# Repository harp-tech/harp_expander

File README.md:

# Harp Input Expander
# Harp Output Expander

Harp board to expand the inputs and outputs of the current harp ecosystem.

# Licensing

The code, designs, documentation, and photos available in this repository is free: you can redistribute it and/or modify it under the terms of the used license.
Each subdirectory will contain a license or, possibly, a set of licenses if it involves both hardware and software. Check files named LICENSE.

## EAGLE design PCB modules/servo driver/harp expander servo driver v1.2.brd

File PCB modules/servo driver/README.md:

# Harp Expander Servo Driver

## Licensing

The designs, documentation, and photos available in this repository are free: you can redistribute it and/or modify it under the terms of the used license.
Check file named LICENSE.

Copyright Filipe Carvalho 2020-2021

<br />This work is licensed under a <a rel="license" href="http://creativecommons.org/licenses/by-nc-sa/3.0/igo/">Creative Commons Attribution-NonCommercial-ShareAlike 3.0 IGO License</a>.

If your are interested in obtaining a license to sell this device, please contact filipe@open-ephys.org

[1]: https://docs.google.com/spreadsheets/d/1aobmmEzBDethzIlrm1eg0eYkBqlyX3s9WbA9KgRwVQI/edit?usp=sharing

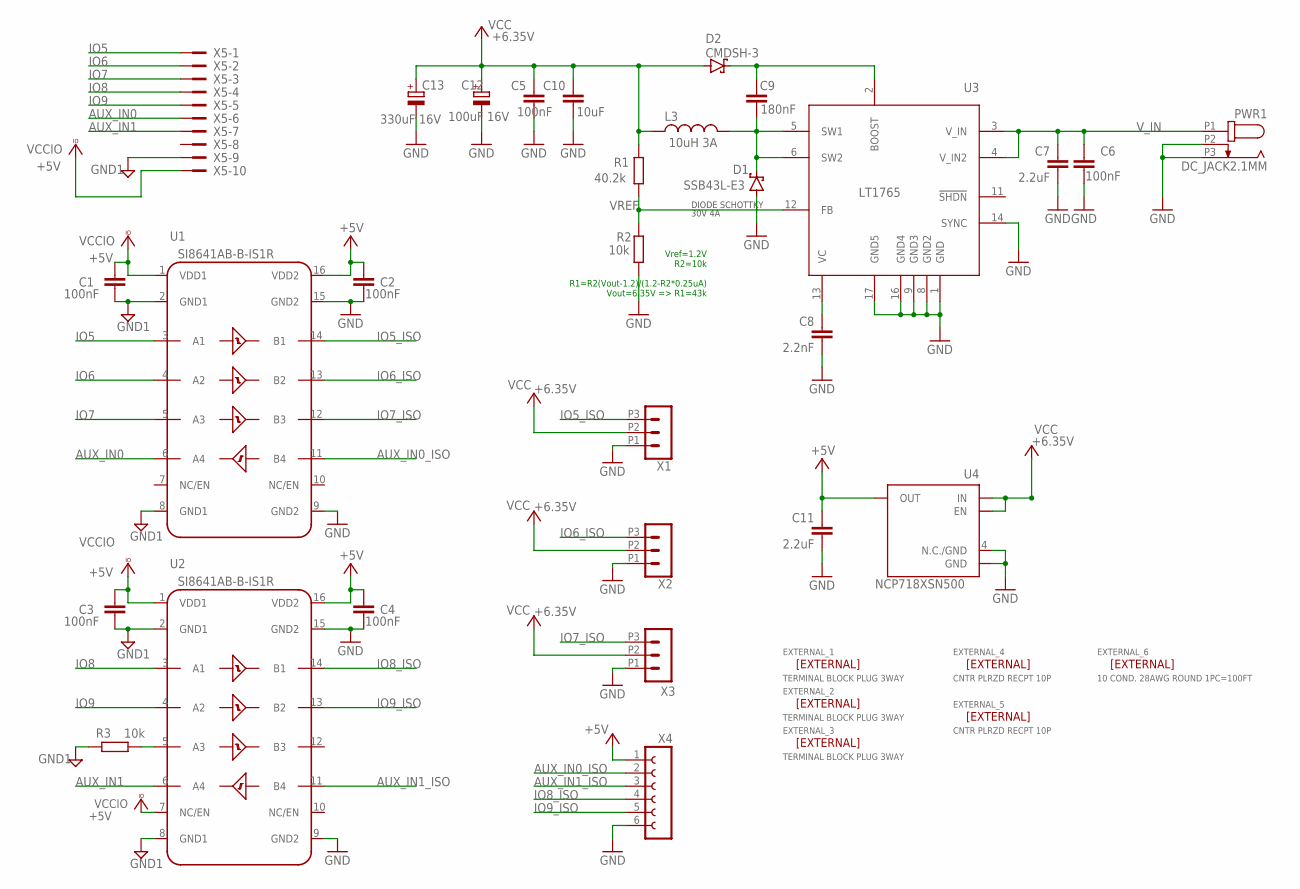
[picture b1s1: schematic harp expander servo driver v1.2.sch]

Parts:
C1, C2, C3, C4, C5, C6: 100nF; C0402; MPN CGA2B3X7R1H104K050BB; DIGIKEY_PN 445-6899-2-ND
C7, C11: 2.2uF; C0603; MPN GRM188R61E225MA12D; DIGIKEY_PN 490-12738-1-ND
C8: 2.2nF; C0402; MPN CL05B222JB5NNNC; DIGIKEY_PN 1276-1532-6-ND
C9: 180nF; C0603; MPN GCG188R91H184KA01D; DIGIKEY_PN 490-GCG188R91H184KA01DCT-ND
C10: 10uF; C0603; MPN EMK107BBJ106MA-T; DIGIKEY_PN 587-3238-1-ND
C12: 100uF 16V; CT7343; MPN T491D107K016AT7280; DIGIKEY_PN 399-18066-1-ND
C13: 330uF 16V; E3,5-8; MPN MCMR16V337M8X7; FARNELL_PN 1870957
D1: SSB43L-E3; SMB; MPN SSB43L-E3/52T; DIGIKEY_PN SSB43L-E3/52TGICT-ND
D2: CMDSH-3; SOD323-R; MPN CMDSH-3; DIGIKEY_PN 1514-CMDSH-3TRPBFREECT-ND
EXTERNAL_1, EXTERNAL_2, EXTERNAL_3: TERMINAL BLOCK PLUG 3WAY; -; MPN 691361100003; DIGIKEY_PN 732-2752-ND
EXTERNAL_4, EXTERNAL_5: CNTR PLRZD RECPT 10P; -; MPN 1658621-1; DIGIKEY_PN AKC10H-ND
EXTERNAL_6: 10 COND. 28AWG ROUND 1PC=100FT; -; MPN 3365/10 100; DIGIKEY_PN 3M157849-100-ND
L3: 10uH 3A; L_IHLP_PADS; MOUSER_PN 70-IHLP2525CZER100M0; DIGIKEY_PN 541-1013-2-ND
PWR1: DC_JACK2.1MM; DC_POWER_INPUT_2.1MM; MPN 163-179PH-EX; DIGIKEY_PN 163-179PH-EX MOUSER
R1: 40.2k; R0402; MPN RC0402FR-0740K2L; DIGIKEY_PN 311-40.2KLRCT-ND
R2, R3: 10k; R0402; MPN CRCW040210K0FKEDC; DIGIKEY_PN 541-3959-1-ND
U1, U2: SI8641AB-B-IS1R; SO16W; MOUSER_PN 634-SI8641AB-B-IS1R; DIGIKEY_PN SI8641AB-B-IS-ND
U3: LT1765; TSSOP16; MPN LT1765EFE#TRPBF; DIGIKEY_PN LT1765EFE#TRPBFCT-ND
U4: NCP718XSN500; SOT23-5; MPN NCP718BSN500T1G; DIGIKEY_PN NCP718BSN500T1GOSCT-ND
X1, X2, X3: CON_3.5MM_1X3; MPN 691322110003; DIGIKEY_PN 732-2770-ND
X4: aux_header; FE06; MPN n.a.
X5: IDC 10WAY STRAIGHT; PAK100/2500-10; MPN SBH11-PBPC-D05-ST-BK; DIGIKEY_PN S9169-ND

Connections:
+5V: C2.1, C4.1, C11.1, U1.16 (VDD2), U2.16 (VDD2), U4.5 (OUT), X4.1
AUX_IN0: U1.6 (A4), X5.6
AUX_IN0_ISO: U1.11 (B4), X4.2
AUX_IN1: U2.6 (A4), X5.7
AUX_IN1_ISO: U2.11 (B4), X4.3
GND: C2.2, C4.2, C5.2, C6.2, C7.2, C8.2, C10.2, C11.2, C12.-, C13.-, D1.A, PWR1.P2 (2), PWR1.P3 (3), R2.1, U1.9 (GND2), U1.15 (GND2), U2.9 (GND2), U2.15 (GND2), U3.1 (GND), U3.8 (GND2), U3.9 (GND3), U3.14 (SYNC), U3.16 (GND4), U3.17 (GND5), U4.2 (GND), U4.4 (N.C./GND), X1.P1 (1), X2.P1 (1), X3.P1 (1), X4.6
GND1: C1.2, C3.2, R3.2, U1.2 (GND1), U1.8 (GND1), U2.2 (GND1), U2.8 (GND1), X5.9
IO5: U1.3 (A1), X5.1
IO5_ISO: U1.14 (B1), X1.P3 (3)
IO6: U1.4 (A2), X5.2
IO6_ISO: U1.13 (B2), X2.P3 (3)
IO7: U1.5 (A3), X5.3
IO7_ISO: U1.12 (B3), X3.P3 (3)
IO8: U2.3 (A1), X5.4
IO8_ISO: U2.14 (B1), X4.4
IO9: U2.4 (A2), X5.5
IO9_ISO: U2.13 (B2), X4.5
unnamed: R3.1, U2.5 (A3)
unnamed: C8.1, U3.13 (VC)
unnamed: C9.2, D1.C, L3.2, U3.5 (SW1), U3.6 (SW2)
unnamed: C9.1, D2.C, U3.2 (BOOST)
VCC: C5.1, C10.1, C12.+, C13.+, D2.A, L3.1, R1.2, U4.1 (IN), U4.3 (EN), X1.P2 (2), X2.P2 (2), X3.P2 (2)
VCCIO: C1.1, C3.1, U1.1 (VDD1), U2.1 (VDD1), U2.7 (NC/EN), X5.10
VREF: R1.1, R2.2, U3.12 (FB)
V_IN: C6.1, C7.1, PWR1.P1 (1), U3.3 (V_IN), U3.4 (V_IN2)

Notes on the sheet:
Vref=1.2V R2=10k R1=R2(Vout-1.2)/(1.2-R2*0.25uA) Vout=6.35V => R1=43k
DIODE SCHOTTKY 30V 4A

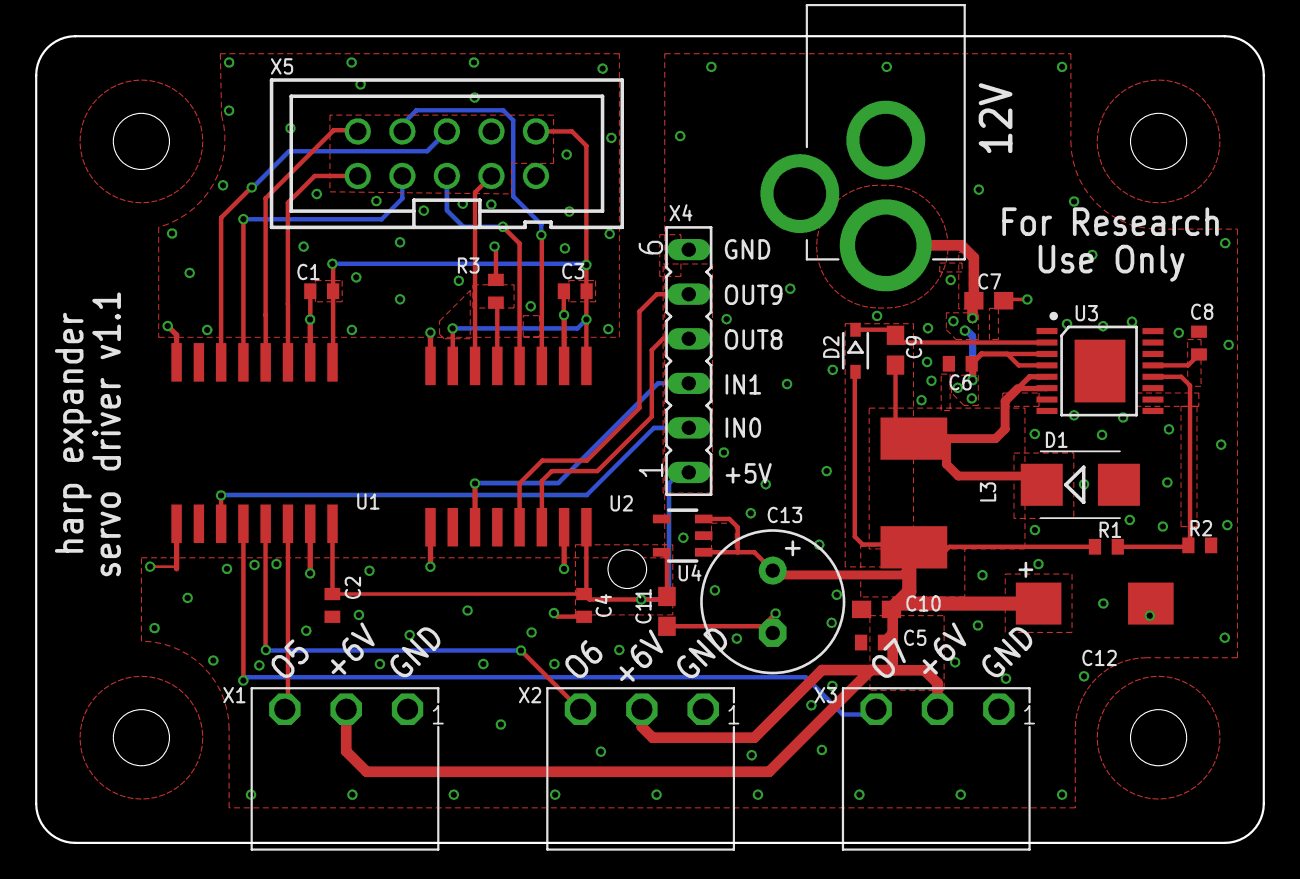
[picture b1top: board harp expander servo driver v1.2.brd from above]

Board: 2 copper layers, 70.0 x 46.0 mm, 35 parts (0 on the bottom side), 25 nets.

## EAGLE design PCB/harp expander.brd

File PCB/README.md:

# Harp Expander PCB

## Licensing

The designs, documentation, and photos available in this repository are free: you can redistribute it and/or modify it under the terms of the used license.
Check file named LICENSE.

Copyright Filipe Carvalho 2020-2021

<br />This work is licensed under a <a rel="license" href="http://creativecommons.org/licenses/by-nc-sa/3.0/igo/">Creative Commons Attribution-NonCommercial-ShareAlike 3.0 IGO License</a>.

If your are interested in obtaining a license to sell this device, please contact filipe@open-ephys.org

[1]: https://docs.google.com/spreadsheets/d/1aobmmEzBDethzIlrm1eg0eYkBqlyX3s9WbA9KgRwVQI/edit?usp=sharing

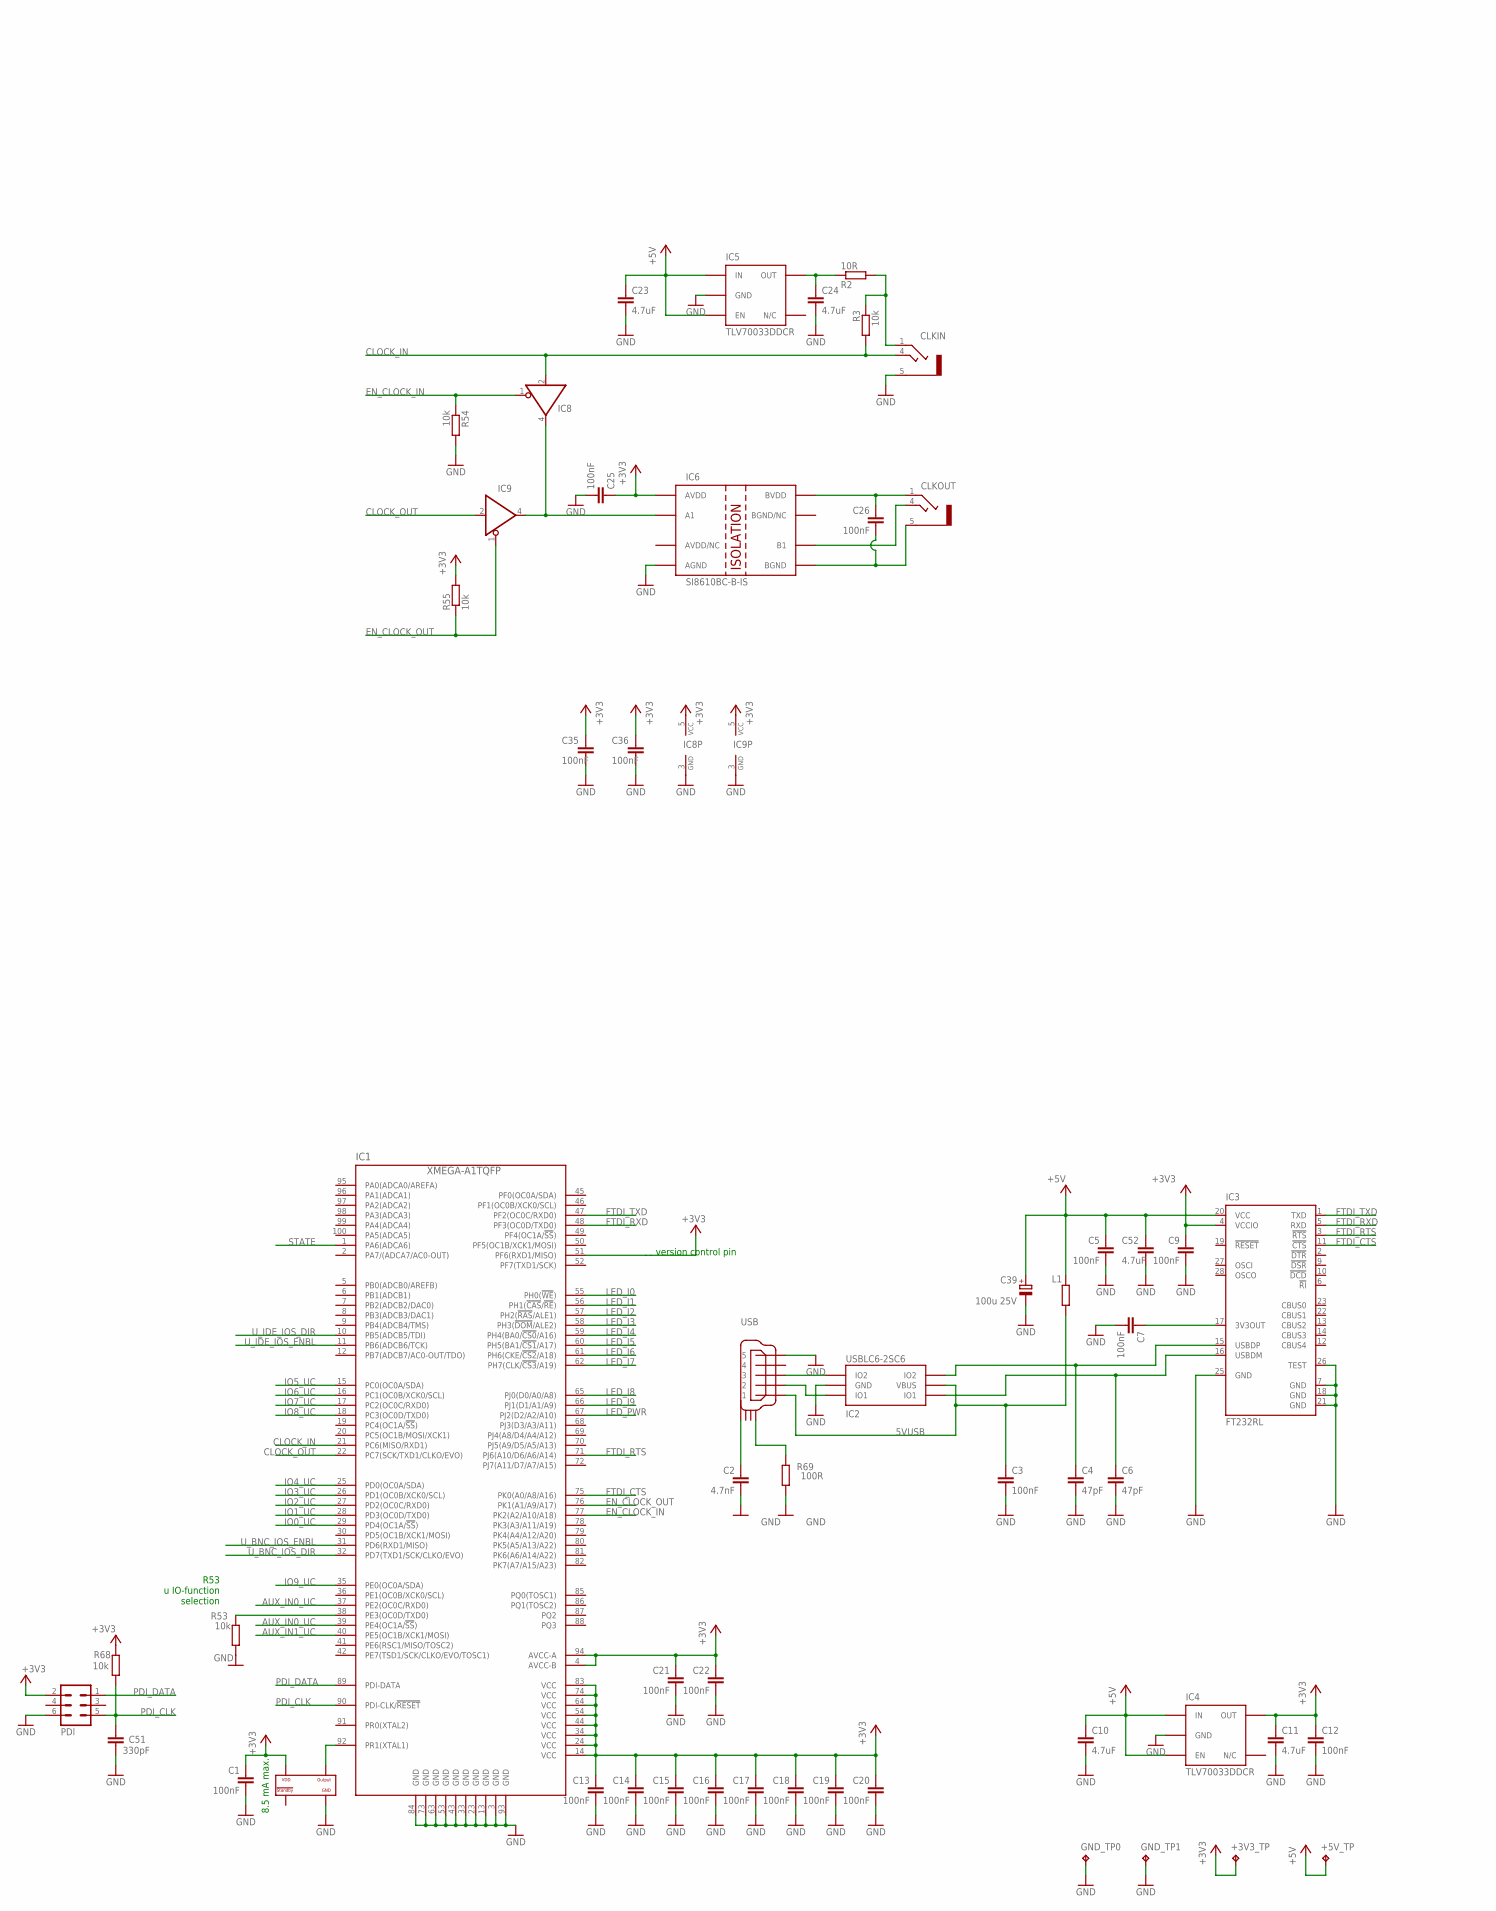
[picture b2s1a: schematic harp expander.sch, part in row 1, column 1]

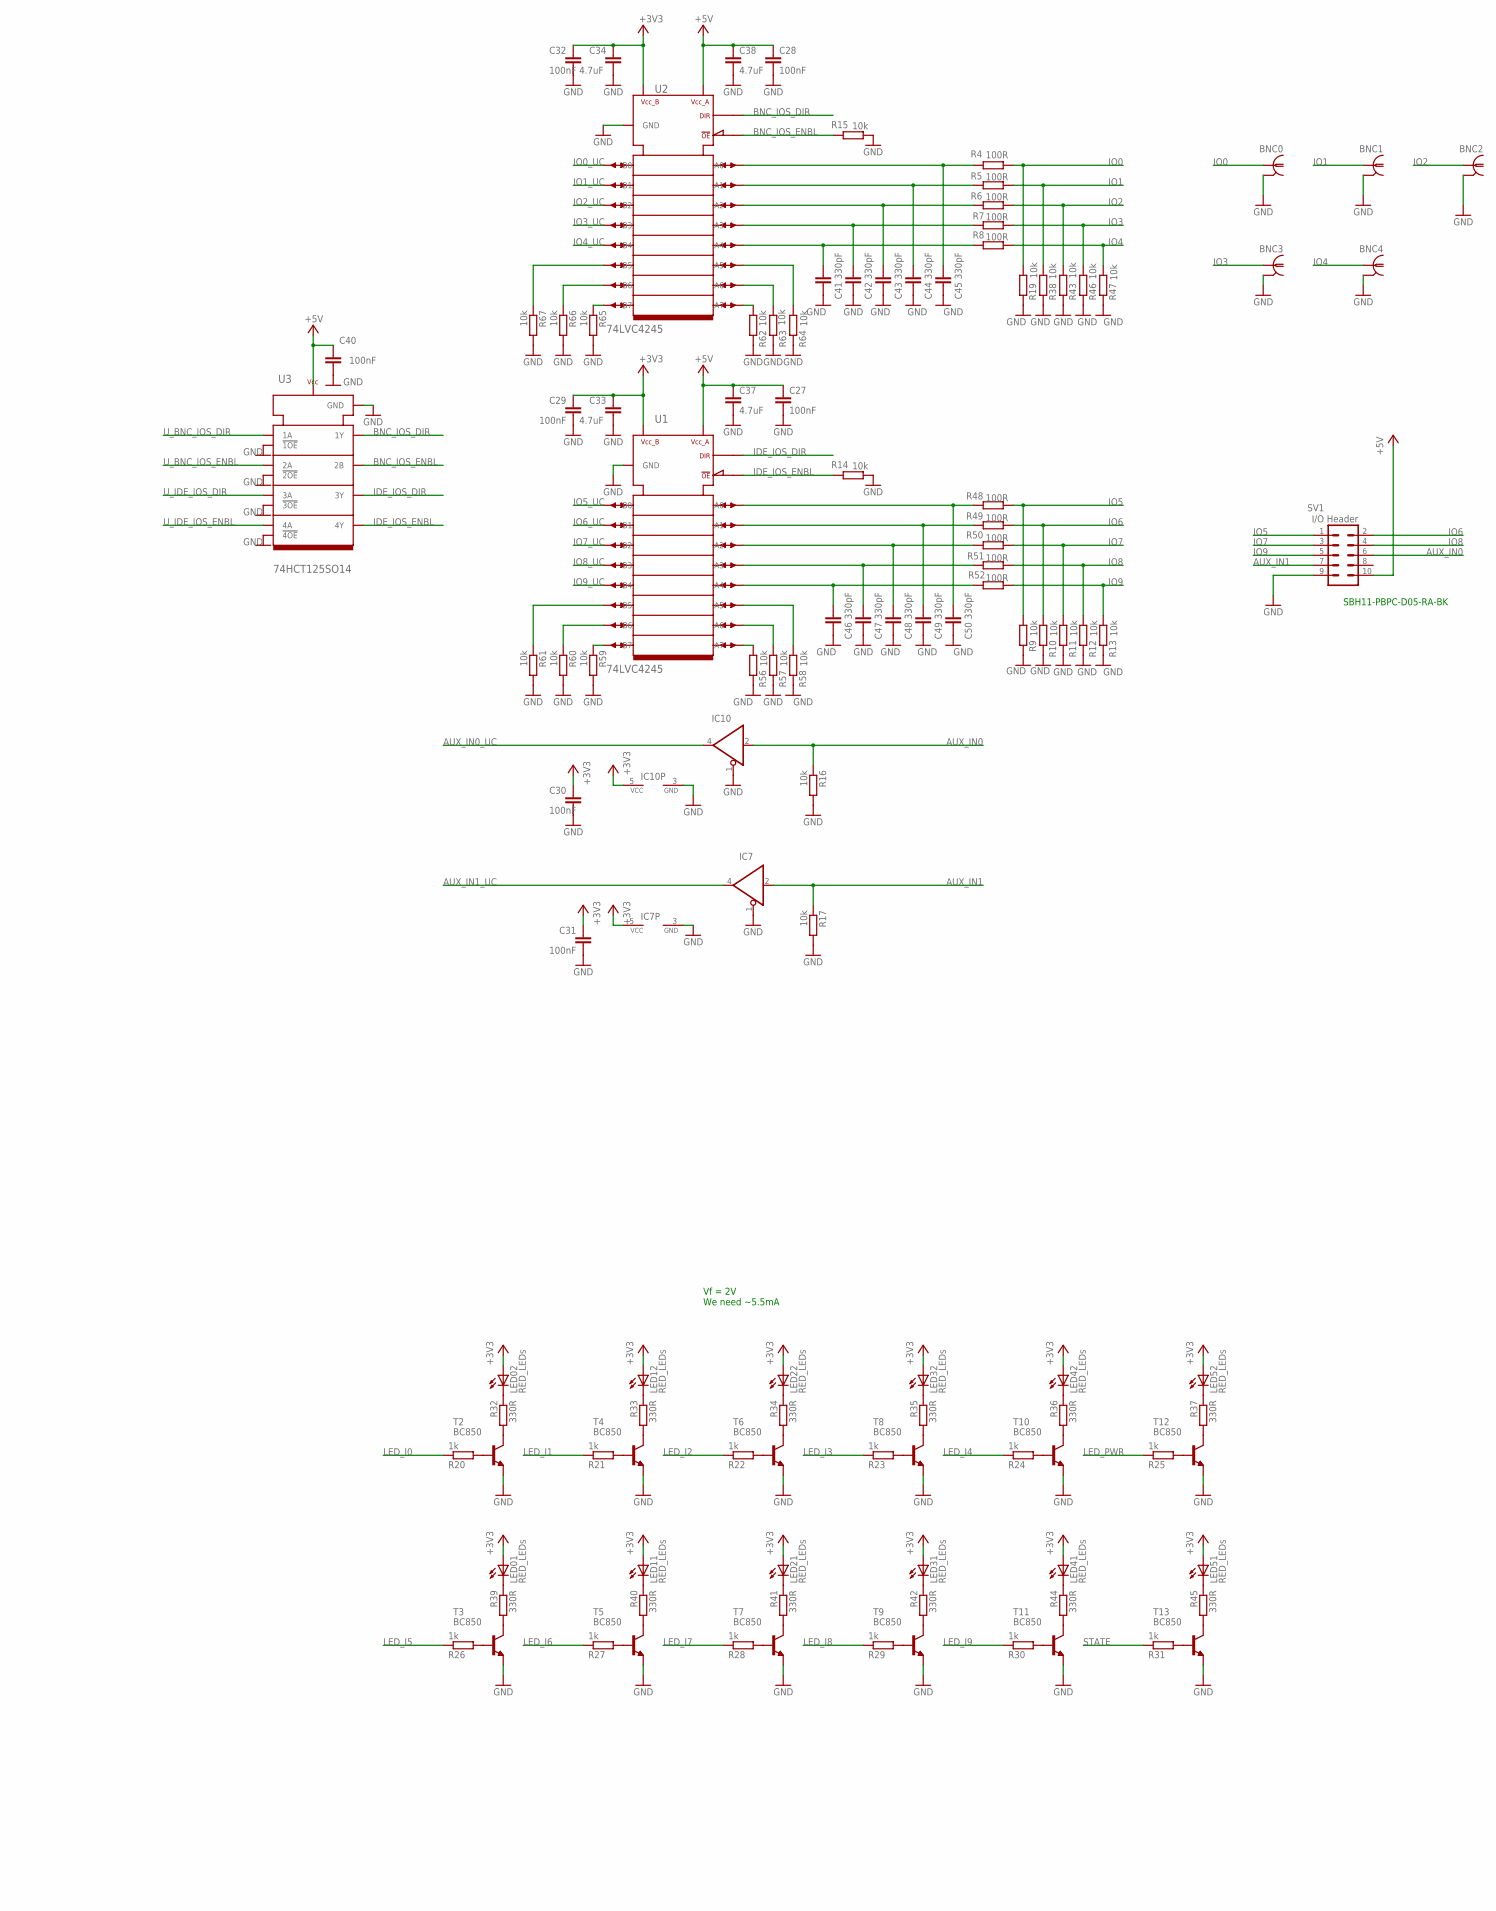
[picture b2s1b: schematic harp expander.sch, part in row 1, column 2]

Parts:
+3V3_TP, +5V_TP: TPPAD1-13; P1-13; MPN n.a.
BNC0, BNC1, BNC2, BNC3, BNC4: BNC plug; 0731000105; MPN 73100-0105
C1, C3, C5, C7, C9, C12, C13, C14, C15, C16, C17, C18, C19, C20, C21, C22, C25, C26, C27, C28, C29, C30, C31, C32, C35, C36, C40: 100nF; C0402; MPN MC0402B104K160CT
C2: 4.7nF; C0402; MPN 885012205084
C4, C6: 47pF; C0402; MPN 04025A470JAT2A
C10, C11, C23, C24, C33, C34, C37, C38, C52: 4.7uF; C0603; MPN C1608X6S1C475K080AC
C39: 100u 25V; TT2D6; MPN EEUFM1E101B
C41, C42, C43, C44, C45, C46, C47, C48, C49, C50, C51: 330pF; C0402; MPN C0402C331J5GACTU
CLKIN: CLCK_JACK; 35RASMT2BHNTRX; MPN 35RASMT2BHNTRX
CLKOUT: CLCK_JACK; 35RASMT2BHNTRX; MPN 35RASMT2BHNTRX
GND_TP0, GND_TP1: TPPAD1-13; P1-13; MPN n.a.
IC1: XMEGA-A1TQFP; TQFP100; MPN ATXMEGA128A1U-AU
IC2: USBLC6-2SC6; SOT23-6L; MPN USBLC6-2SC6
IC3: FT232RL; SSOP28; MPN FT232RL-REEL
IC4, IC5: TLV70033DDCR; TSOT23-5; MPN TLV70033DDCR
IC6: SI8610BC-B-IS; SO-08; MPN SI8610EC-B-IS
IC7, IC8, IC9, IC10: SN74LVC1G125DBVT; SOT23-5; MPN SN74LVC1G125DBVT
L1: 40R@100MHz; R0805; MPN MI0805K400R-10
LED0, LED1, LED2, LED3, LED4, LED5: RED_LEDs; 569-011X-X00_LED_ARRAY; MPN 5690-111-100F
OSC: Oscillator; OSCILLATOR_3.2X2.5; MPN O 32,0-JT32C-A-K-3,3-LF
PDI: PROG HEADER; MA03-2; MPN 67996-206HLF
R2: 10R; R0402; MPN CRCW040210R0FKEDHP
R3, R9, R10, R11, R12, R13, R14, R15, R16, R17, R19, R38, R43, R46, R47, R53, R54, R55, R56, R57, R58, R59, R60, R61, R62, R63, R64, R65, R66, R67, R68: 10k; R0402; MPN CRCW040210K0FKED
R4, R5, R6, R7, R8, R48, R49, R50, R51, R52, R69: 100R; R0603; MPN CRCW0603100RFKEAHP
R20, R21, R22, R23, R24, R25, R26, R27, R28, R29, R30, R31: 1k; R0402; MPN CRCW04021K00FKED
R32, R33, R34, R35, R36, R37, R39, R40, R41, R42, R44, R45: 330R; R0402; MPN RC0402FR-07330RL
SV1: I/O Header; ML10L; MPN SBH11-PBPC-D05-RA-BK
T2, T3, T4, T5, T6, T7, T8, T9, T10, T11, T12, T13: BC850; SOT23; MPN BC850C,215
U1, U2: 744245X; SO24L; MPN 74LVC4245AD,118
U3: 74HCT125SO14; SO14; MPN 74HCT125D,653
USB: mini USB; 240-0002-1; MPN UX60-MB-5S8

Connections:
5VUSB: C3.1, IC2.P$5 (VBUS), L1.2, USB.P$1 (1)
+3V3: +3V3_TP.TP, C1.1, C9.1, C11.1, C12.1, C13.1, C14.1, C15.1, C16.1, C17.1, C18.1, C19.1, C20.1, C21.1, C22.1, C25.1, C29.1, C30.1, C31.1, C32.1, C33.1, C34.1, C35.1, C36.1, IC1.4 (AVCC-B), IC1.14 (VCC), IC1.24 (VCC), IC1.34 (VCC), IC1.44 (VCC), IC1.51 (PF6(RXD1/MISO)), IC1.54 (VCC), IC1.64 (VCC), IC1.74 (VCC), IC1.83 (VCC), IC1.94 (AVCC-A), IC3.4 (VCCIO), IC4.5 (OUT), IC6.1 (AVDD), IC7.5 (VCC), IC8.5 (VCC), IC9.5 (VCC), IC10.5 (VCC), LED0.A1 (A), LED0.A2 (A), LED1.A1 (A), LED1.A2 (A), LED2.A1 (A), LED2.A2 (A), LED3.A1 (A), LED3.A2 (A), LED4.A1 (A), LED4.A2 (A), LED5.A1 (A), LED5.A2 (A), OSC.P$4 (VDD), PDI.2, R55.2, R68.2, U1.23 (VCC_B), U1.24 (VCC_B), U2.23 (VCC_B), U2.24 (VCC_B)
+5V: +5V_TP.TP, C5.1, C10.1, C23.1, C27.1, C28.1, C37.1, C38.1, C39.+, C40.1, C52.1, IC3.20 (VCC), IC4.1 (IN), IC4.3 (EN), IC5.1 (IN), IC5.3 (EN), L1.1, SV1.10, U1.1 (VCC_A), U2.1 (VCC_A), U3.14 (VCC)
AUX_IN0: IC10.2 (I), R16.1, SV1.6
AUX_IN0_UC: IC1.37 (PE2(OC0C/RXD0)), IC1.39 (PE4(OC1A/!SS!)), IC10.4 (O)
AUX_IN1: IC7.2 (I), R17.1, SV1.7
AUX_IN1_UC: IC1.40 (PE5(OC1B/XCK1/MOSI)), IC7.4 (O)
BNC_IOS_DIR: U2.2 (DIR), U3.3 (1Y)
BNC_IOS_ENBL: R15.2, U2.22 (OE), U3.6 (2B)
CLOCK_IN: CLKIN.4, IC1.21 (PC6(MISO/RXD1)), IC8.2 (I), R3.2
CLOCK_OUT: IC1.22 (PC7(SCK/TXD1/CLKO/EVO)), IC9.2 (I)
EN_CLOCK_IN: IC1.77 (PK2(A2/A10/A18)), IC8.1 (OE), R54.1
EN_CLOCK_OUT: IC1.76 (PK1(A1/A9/A17)), IC9.1 (OE), R55.1
FTDI_CTS: IC1.75 (PK0(A0/A8/A16)), IC3.11 (!CTS)
FTDI_RTS: IC1.71 (PJ6(A10/D6/A6/A14)), IC3.3 (!RTS)
FTDI_RXD: IC1.48 (PF3(OC0D/TXD0)), IC3.5 (RXD)
FTDI_TXD: IC1.47 (PF2(OC0C/RXD0)), IC3.1 (TXD)
GND: BNC0.2, BNC0.3 (2), BNC1.2, BNC1.3 (2), BNC2.2, BNC2.3 (2), BNC3.2, BNC3.3 (2), BNC4.2, BNC4.3 (2), C1.2, C2.2, C3.2, C4.2, C5.2, C6.2, C7.2, C9.2, C10.2, C11.2, C12.2, C13.2, C14.2, C15.2, C16.2, C17.2, C18.2, C19.2, C20.2, C21.2, C22.2, C23.2, C24.2, C25.2, C27.2, C28.2, C29.2, C30.2, C31.2, C32.2, C33.2, C34.2, C35.2, C36.2, C37.2, C38.2, C39.-, C40.2, C41.2, C42.2, C43.2, C44.2, C45.2, C46.2, C47.2, C48.2, C49.2, C50.2, C51.2, C52.2, CLKIN.5, GND_TP0.TP, GND_TP1.TP, IC1.3 (GND), IC1.13 (GND), IC1.23 (GND), IC1.33 (GND), IC1.43 (GND), IC1.53 (GND), IC1.63 (GND), IC1.73 (GND), IC1.84 (GND), IC1.93 (GND), IC2.P$2 (GND), IC3.7 (GND), IC3.18 (GND), IC3.21 (GND), IC3.25 (GND), IC3.26 (TEST), IC4.2 (GND), IC5.2 (GND), IC6.4 (AGND), IC7.1 (OE), IC7.3 (GND), IC8.3 (GND), IC9.3 (GND), IC10.1 (OE), IC10.3 (GND), OSC.P$2 (GND), PDI.6, R9.2, R10.2, R11.2, R12.2, R13.2, R14.1, R15.1, R16.2, R17.2, R19.1, R38.1, R43.1, R46.1, R47.1, R53.2, R54.2, R56.2, R57.2, R58.2, R59.2, R60.2, R61.2, R62.2, R63.2, R64.2, R65.2, R66.2, R67.2, R69.2, SV1.9, T2.2 (E), T3.2 (E), T4.2 (E), T5.2 (E), T6.2 (E), T7.2 (E), T8.2 (E), T9.2 (E), T10.2 (E), T11.2 (E), T12.2 (E), T13.2 (E), U1.11 (GND), U1.12 (GND), U1.13 (GND), U2.11 (GND), U2.12 (GND), U2.13 (GND), U3.1 (!1OE), U3.4 (!2OE), U3.7 (GND), U3.10 (!3OE), U3.13 (!4OE), USB.P$5 (5)
GND_ISO: C26.2, CLKOUT.5, IC6.5 (BGND)
IDE_IOS_DIR: U1.2 (DIR), U3.8 (3Y)
IDE_IOS_ENBL: R14.2, U1.22 (OE), U3.11 (4Y)
IO0: BNC0.1, R4.1, R19.2
IO0_UC: IC1.29 (PD4(OC1A/!SS!)), U2.21 (B0)
IO1: BNC1.1, R5.1, R38.2
IO1_UC: IC1.28 (PD3(OC0D/TXD0)), U2.20 (B1)
IO2: BNC2.1, R6.1, R43.2
IO2_UC: IC1.27 (PD2(OC0C/RXD0)), U2.19 (B2)
IO3: BNC3.1, R7.1, R46.2
IO3_UC: IC1.26 (PD1(OC0B/XCK0/SCL)), U2.18 (B3)
IO4: BNC4.1, R8.1, R47.2
IO4_UC: IC1.25 (PD0(OC0A/SDA)), U2.17 (B4)
IO5: R9.1, R48.1, SV1.1
IO5_UC: IC1.15 (PC0(OC0A/SDA)), U1.21 (B0)
IO6: R10.1, R49.1, SV1.2
IO6_UC: IC1.16 (PC1(OC0B/XCK0/SCL)), U1.20 (B1)
IO7: R11.1, R50.1, SV1.3
IO7_UC: IC1.17 (PC2(OC0C/RXD0)), U1.19 (B2)
IO8: R12.1, R51.1, SV1.4
IO8_UC: IC1.18 (PC3(OC0D/TXD0)), U1.18 (B3)
IO9: R13.1, R52.1, SV1.5
IO9_UC: IC1.35 (PE0(OC0A/SDA)), U1.17 (B4)
LED_I0: IC1.55 (PH0(!WE!)), R20.1
LED_I1: IC1.56 (PH1(!CAS!/!RE!)), R21.1
LED_I2: IC1.57 (PH2(!RAS!/ALE1)), R22.1
LED_I3: IC1.58 (PH3(!DOM!/ALE2)), R23.1
LED_I4: IC1.59 (PH4(BA0/!CS0!/A16)), R24.1
LED_I5: IC1.60 (PH5(BA1/!CS1!/A17)), R26.1
LED_I6: IC1.61 (PH6(CKE/!CS2!/A18)), R27.1
LED_I7: IC1.62 (PH7(CLK/!CS3!/A19)), R28.1
LED_I8: IC1.65 (PJ0(D0/A0/A8)), R29.1
LED_I9: IC1.66 (PJ1(D1/A1/A9)), R30.1
LED_PWR: IC1.67 (PJ2(D2/A2/A10)), R25.1
unnamed: R24.2, T10.1 (B)
unnamed: CLKOUT.4, IC6.6 (B1)
unnamed: R20.2, T2.1 (B)
unnamed: LED0.C2 (C), R32.1
unnamed: C26.1, CLKOUT.1, IC6.8 (BVDD)
unnamed: C50.1, R48.2, U1.3 (A0)
unnamed: R36.2, T10.3 (C)
unnamed: R32.2, T2.3 (C)
unnamed: IC1.38 (PE3(OC0D/TXD0)), R53.1
unnamed: R26.2, T3.1 (B)
unnamed: R22.2, T6.1 (B)
unnamed: R39.2, T3.3 (C)
unnamed: R21.2, T4.1 (B)
unnamed: LED3.C1 (C), R42.1
unnamed: R33.2, T4.3 (C)
unnamed: R27.2, T5.1 (B)
unnamed: R34.2, T6.3 (C)
unnamed: R40.2, T5.3 (C)
unnamed: LED3.C2 (C), R35.1
unnamed: R28.2, T7.1 (B)
unnamed: R41.2, T7.3 (C)
unnamed: R23.2, T8.1 (B)
unnamed: R35.2, T8.3 (C)
unnamed: R29.2, T9.1 (B)
unnamed: R42.2, T9.3 (C)
unnamed: LED1.C2 (C), R33.1
unnamed: LED2.C2 (C), R34.1
unnamed: LED1.C1 (C), R40.1
unnamed: LED2.C1 (C), R41.1
unnamed: R30.2, T11.1 (B)
unnamed: LED0.C1 (C), R39.1
unnamed: C7.1, IC3.17 (3V3OUT)
unnamed: IC2.P$1 (IO1), USB.P$2 (2)
unnamed: CLKIN.1, R2.2, R3.1
unnamed: C24.1, IC5.5 (OUT), R2.1
unnamed: IC6.2 (A1), IC8.4 (O), IC9.4 (O)
unnamed: R44.2, T11.3 (C)
unnamed: IC2.P$3 (IO2), USB.P$3 (3)
unnamed: R25.2, T12.1 (B)
unnamed: R37.2, T12.3 (C)
unnamed: R31.2, T13.1 (B)
unnamed: C2.1, USB.SHIELD_4
unnamed: R45.2, T13.3 (C)
unnamed: R69.1, USB.SHIELD_1
unnamed: LED5.C1 (C), R45.1
unnamed: LED5.C2 (C), R37.1
unnamed: LED4.C2 (C), R36.1
unnamed: LED4.C1 (C), R44.1
unnamed: C49.1, R49.2, U1.4 (A1)
unnamed: C48.1, R50.2, U1.5 (A2)
unnamed: C47.1, R51.2, U1.6 (A3)
unnamed: C46.1, R52.2, U1.7 (A4)
unnamed: C45.1, R4.2, U2.3 (A0)
unnamed: C44.1, R5.2, U2.4 (A1)
unnamed: C43.1, R6.2, U2.5 (A2)
unnamed: R61.1, U1.16 (B5)
unnamed: C42.1, R7.2, U2.6 (A3)
unnamed: R60.1, U1.15 (B6)
unnamed: R59.1, U1.14 (B7)
unnamed: R56.1, U1.10 (A7)
unnamed: C41.1, R8.2, U2.7 (A4)
unnamed: R57.1, U1.9 (A6)
unnamed: R58.1, U1.8 (A5)
unnamed: R62.1, U2.10 (A7)
unnamed: R63.1, U2.9 (A6)
unnamed: R64.1, U2.8 (A5)
unnamed: R67.1, U2.16 (B5)
unnamed: R66.1, U2.15 (B6)
unnamed: R65.1, U2.14 (B7)
OSC1: IC1.92 (PR1(XTAL1)), OSC.P$3 (OUTPUT)
PDI_CLK: C51.1, IC1.90 (PDI-CLK/!RESET), PDI.5, R68.1
PDI_DATA: IC1.89 (PDI-DATA), PDI.1
STATE: IC1.1 (PA6(ADCA6)), R31.1
USBDM: C6.1, IC2.P$6 (IO1), IC3.16 (USBDM)
USBDP: C4.1, IC2.P$4 (IO2), IC3.15 (USBDP)
U_BNC_IOS_DIR: IC1.32 (PD7(TXD1/SCK/CLKO/EVO)), U3.2 (1A)
U_BNC_IOS_ENBL: IC1.31 (PD6(RXD1/MISO)), U3.5 (2A)
U_IDE_IOS_DIR: IC1.10 (PB5(ADCB5/TDI)), U3.9 (3A)
U_IDE_IOS_ENBL: IC1.11 (PB6(ADCB6/TCK)), U3.12 (4A)

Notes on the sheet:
Vf = 2V We need ~5.5mA
8.5 mA max.
SBH11-PBPC-D05-RA-BK
R53 u IO-function selection
version control pin

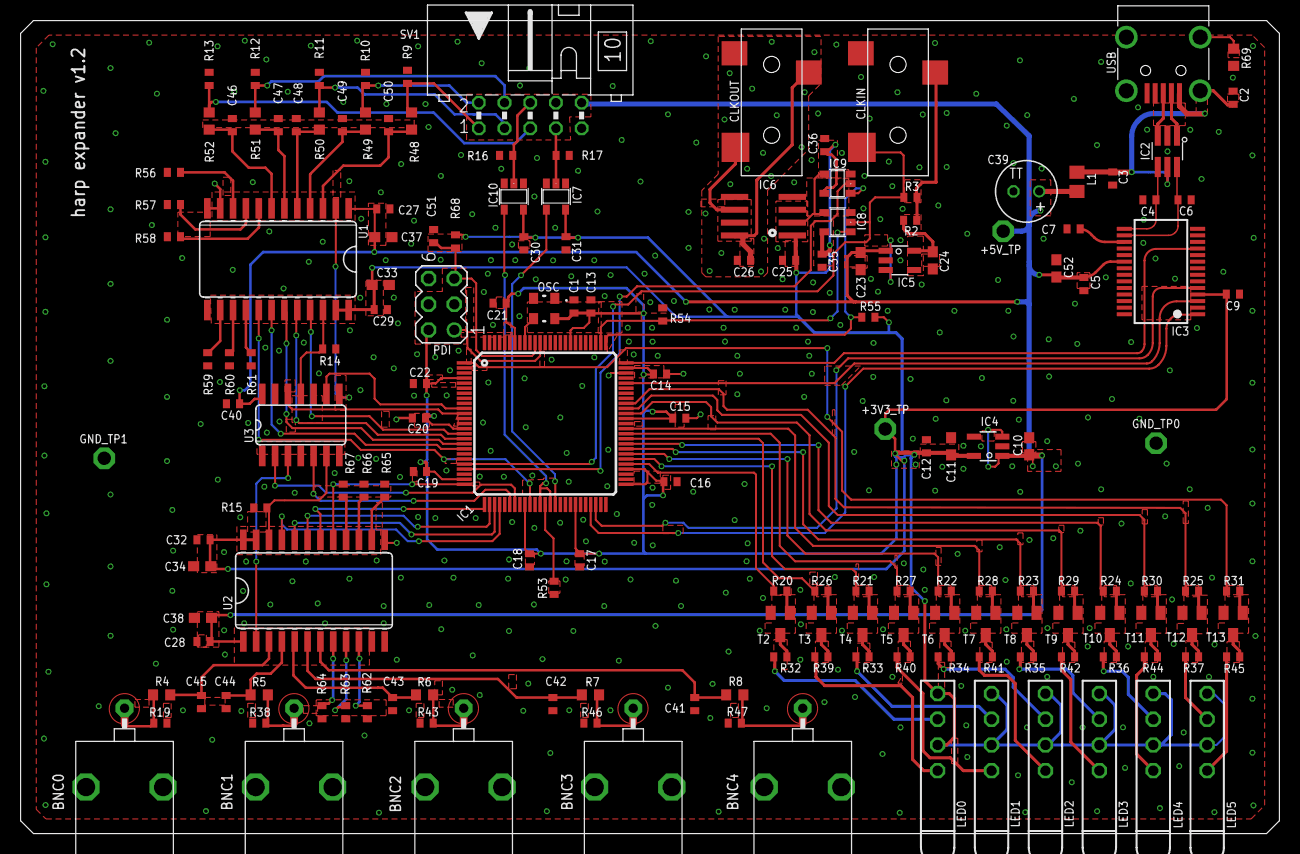
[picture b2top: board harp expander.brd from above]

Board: 2 copper layers, 124.5 x 80.4 mm, 165 parts (0 on the bottom side), 131 nets.

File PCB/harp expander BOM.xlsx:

Qty | Value | Package | Parts | MPN | Type
PCB COMPONENTS
5 | BNC plug |  | BNC0, BNC1, BNC2, BNC3, BNC4 | 73100-0105 | TH
27 | 100nF | C0402 | C1, C3, C5, C7, C9, C12, C13, C14, C15, C16, C17, C18, C19, C20, C21, C22, C25,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 | MC0402B104K160CT | SMD
9 | 4.7uF | C0603 | C10, C11, C23, C24, C33, C34, C37, C38, C52 | C1608X6S1C475K080AC | SMD
1 | 4.7nF | C0402 | C2 | 885012205084 | SMD
1 | 100u 25V | TT2D6 | C39 | EEUFM1E101B | TH
2 | 47pF | C0402 | C4, C6 | 04025A470JAT2A | SMD
11 | 330pF | C0402 | C41, C42, C43, C44, C45, C46, C47, C48, C49, C50, C51 | C0402C331J5GACTU | SMD
2 | CLCK_JACK | 35RASMT2BHNTRX | CLKIN, CLKOUT | 35RASMT2BHNTRX | SMD
1 | XMEGA-A1TQFP | TQFP100 | IC1 | ATXMEGA128A1U-AU | SMD
1 | USBLC6-2SC6 | SOT23-6L | IC2 | USBLC6-2SC6 | SMD
1 | FT232RL | SSOP28 | IC3 | FT232RL-REEL | SMD
2 | TLV70033DDCR | TSOT23-5 | IC4, IC5 | TLV70033DDCR | SMD
1 | SI8610BC-B-IS | SO-08 | IC6 | SI8610EC-B-IS | SMD
4 | SN74LVC1G125DBVT | SOT23-5 | IC7, IC8, IC9, IC10 | SN74LVC1G125DBVT | SMD
1 | 40R@100MHz | R0805 | L1 | MI0805K400R-10 | SMD
6 | RED_LEDs | 569-011X-X00_LED_ARRAY | LED0, LED1, LED2, LED3, LED4, LED5 | 5690-111-100F | TH
1 | Oscillator | OSCILLATOR_3.2X2.5 | OSC | O 32,0-JT32C-A-K-3,3-LF | SMD | Alternative: DSC1001CI5-032.0000T
1 | PROG HEADER | MA03-2 | PDI | 67996-206HLF | TH
1 | 10R | R0402 | R2 | CRCW040210R0FKEDHP | SMD
12 | 1k | R0402 | R20, R21, R22, R23, R24, R25, R26, R27, R28, R29, R30, R31 | CRCW04021K00FKED | SMD
31 | 10k | R0402 | R3, R9, R10, R11, R12, R13, R14, R15, R16, R17, R19, R38, R43, R46, R47, R53, R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 | CRCW040210K0FKED | SMD
12 | 330R | R0402 | R32, R33, R34, R35, R36, R37, R39, R40, R41, R42, R44, R45 | RC0402FR-07330RL | SMD
11 | 100R | R0603 | R4, R5, R6, R7, R8, R48, R49, R50, R51, R52, R69 | CRCW0603100RFKEAHP | SMD
1 | I/O Header | ML10L | SV1 | SBH11-PBPC-D05-RA-BK | TH
12 | BC850 | SOT23 | T2, T3, T4, T5, T6, T7, T8, T9, T10, T11, T12, T13 | BC850C,215 | SMD
2 | 744245X | SO24L | U1, U2 | 74LVC4245AD,118 | SMD
1 | 74HCT125SO14 | SO14 | U3 | 74HCT125D,653 | SMD
1 | mini USB | 240-0002-1 | USB | UX60-MB-5S8 | SMD
1 |  |  | PCB
POST-PRODUCTION
1 |  |  | Front Panel PCB | PCBWAY
1 |  |  | Rear Panel PCB | PCBWAY
1 |  |  | Enclosure | B5-080BK
4 |  |  | Bumper Cylindrical Dome 9.53mm | SJ-5306-CLEAR-3000/CASE
ACCESSORIES
1 |  |  | 3.5mm stereo jack cable 1.2 m, Black | AV13646
1 |  |  | 0.9 left angle USB cable | USB2HABM3RA
NOTES
 |  |  |  | Number of unique parts | 28
 |  |  |  | Number of unique SMD parts | 23
 |  |  |  | Number of unique TH parts | 5
 |  |  |  | Number of SMD parts | 147
 |  |  |  | Number of TH parts | 14

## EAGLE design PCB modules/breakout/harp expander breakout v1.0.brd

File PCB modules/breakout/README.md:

# Harp Expander Breakout

## Licensing

The designs, documentation, and photos available in this repository are free: you can redistribute it and/or modify it under the terms of the used license.
Check file named LICENSE.

Copyright Filipe Carvalho 2020-2021

<br />This work is licensed under a <a rel="license" href="http://creativecommons.org/licenses/by-nc-sa/3.0/igo/">Creative Commons Attribution-NonCommercial-ShareAlike 3.0 IGO License</a>.

If your are interested in obtaining a license to sell this device, please contact filipe@open-ephys.org

[1]: https://docs.google.com/spreadsheets/d/1aobmmEzBDethzIlrm1eg0eYkBqlyX3s9WbA9KgRwVQI/edit?usp=sharing

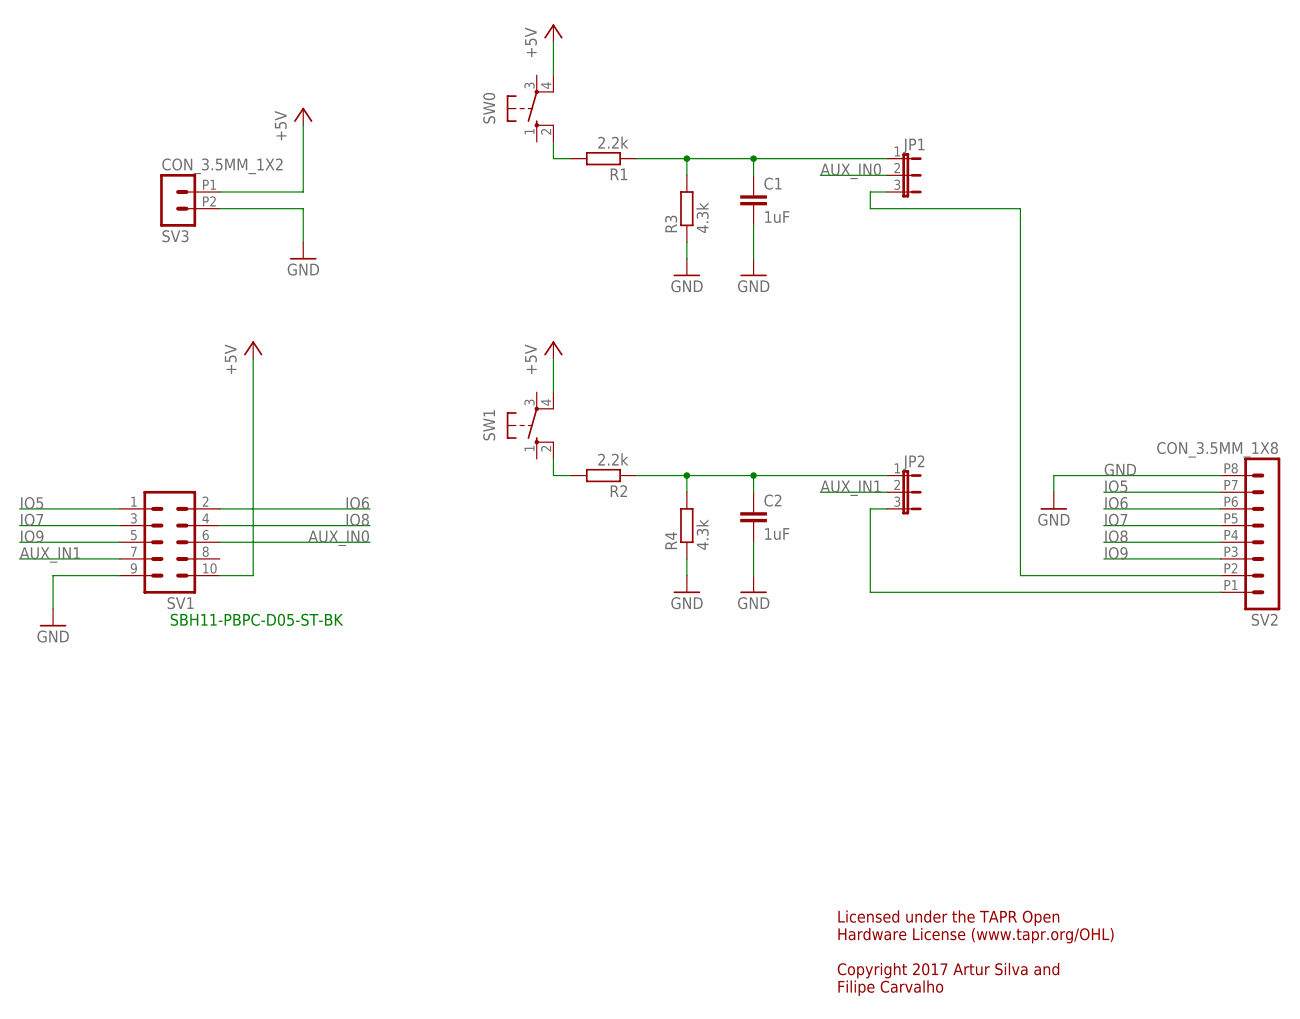
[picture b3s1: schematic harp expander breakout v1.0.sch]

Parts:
C1, C2: 1uF; C0603
JP1, JP2: JP2E; JP2
R1, R2: 2.2k; R0603
R3, R4: 4.3k; R0603
SV1: ML10
SV2: CON_3.5MM_1X8
SV3: CON_3.5MM_1X2
SW0: 40-XX; B3F-40XX; MPN B3F-4000
SW1: 40-XX; B3F-40XX

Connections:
+5V: SV1.10, SV3.P1 (1), SW0.4 (P1), SW1.4 (P1)
AUX_IN0: JP1.2, SV1.6
AUX_IN0_CONNECTOR: JP1.3, SV2.P2 (2)
AUX_IN1: JP2.2, SV1.7
AUX_IN1_CONNECTOR: JP2.3, SV2.P1 (1)
GND: C1.2, C2.2, R3.1, R4.1, SV1.9, SV2.P8 (8), SV3.P2 (2)
IO5: SV1.1, SV2.P7 (7)
IO6: SV1.2, SV2.P6 (6)
IO7: SV1.3, SV2.P5 (5)
IO8: SV1.4, SV2.P4 (4)
IO9: SV1.5, SV2.P3 (3)
unnamed: R2.2, SW1.2 (S1)
unnamed: C2.1, JP2.1, R2.1, R4.2
unnamed: R1.2, SW0.2 (S1)
unnamed: C1.1, JP1.1, R1.1, R3.2

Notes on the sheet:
Licensed under the TAPR Open Hardware License (www.tapr.org/OHL) Copyright 2017 Artur Silva and Filipe Carvalho
SBH11-PBPC-D05-ST-BK

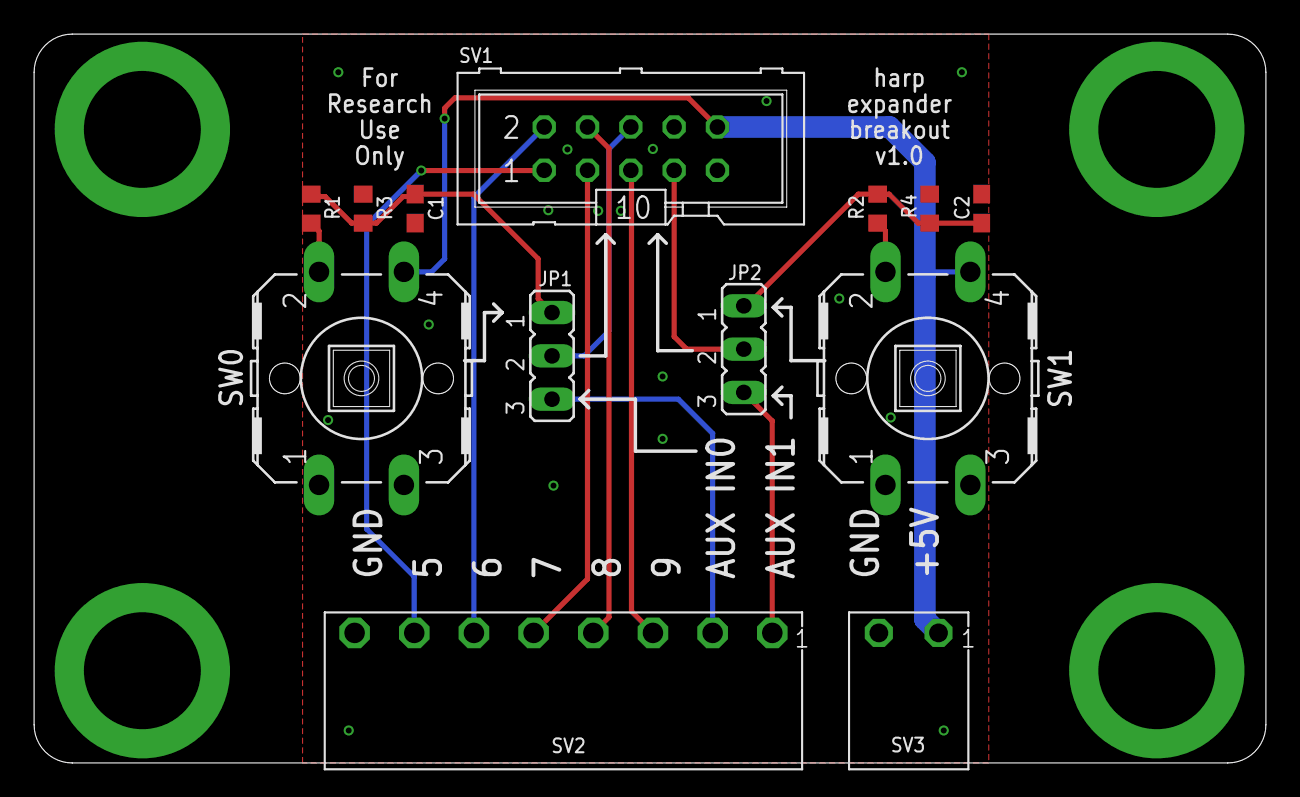
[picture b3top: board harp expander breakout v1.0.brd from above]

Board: 2 copper layers, 72.2 x 42.8 mm, 13 parts (0 on the bottom side), 15 nets.
